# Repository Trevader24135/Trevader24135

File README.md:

Hi! I'm Trevor (@Trevader24135)

I have a bachelor's degree in Electrical Engineering, and have been programming since I was 8 years old! My current obsession is with Rust, but Python has cemented a place in my heart as my first love.

I love Digital Signal Processing, and performing real-time signal analysis for Software-Defined-Radio operations is my area of expertise. I would like to learn more about FPGAs to do the specialized processing more efficiently there, but doing it simply on a CPU (or GPU!) in a compiled language is good enough for most of my day-to-day use cases.

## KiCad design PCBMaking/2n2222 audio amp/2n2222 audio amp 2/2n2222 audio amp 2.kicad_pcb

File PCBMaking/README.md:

# PCBMaking

Recently, I tried making a mini-CNC to mill PCBs. This project ended up failing, mostly due to it not being stiff enough. I likely cheaped out too much on the materials, and probably the spindle too. It worked a bit though, and I tried milling a few PCBs with mixed results. Honestly, mostly negative, but at least I gained some experience with the open-source KiCad software for designing PCBs, which was quite a bit of fun.

<table>
    <tr>
        <td>Project</td>
        <td>Description</td>
    </tr>
    <tr>
        <td>2n2222 audio amp</td>
        <td>This project was meant to be a simple test of my PCB milling capabilities. I actually managed to get a somewhat successful PCB from this one, but it didn't work that well. Probably because I hadn't learned transistor-based circuit analysis and I honestly didn't know what I was doing. It was neat to see it come together though.</td>
    </tr>
    <tr>
        <td>ATmega8U2 breakout</td>
        <td>Had my milling proven more successful and able to mill smaller traces, I was sort of planning on getting some ATmega 8U2 ICs and putting them on breakout boards to use in projects. Oh well, I'll do that when I build an actually-working mill.</td>
    </tr>
    <tr>
        <td>CNC-Trace-Stress-Test</td>
        <td>This was a simple stress test of basic traces of varying thicknesses. I managed to mostly get the 0.4mm trace, but I more reliably managed the 0.5 and larger. Though, this was with a wide clearance, and I couldn't put them as close as I wanted.</td>
    </tr>
    <tr>
        <td>RGB-ShiftRegister</td>
        <td>More of a test of my PCB-making skills, I designed this simple board to try to multiplex some RGB LEDs with a shift register and a microcontroller. This never made it to production as the traces were too close and small for my crappy PCB-mill.</td>
    </tr>
    <tr>
        <td>ShiftRegisterLEDs</td>
        <td>Same concept as the last one, but simplified to have a better chance of working. No transistors and no RGB, just simple LEDs to test it out. It still never made production.</td>
    </tr>
    <tr>
        <td>TylerMoon</td>
        <td>If the PCB milling had worked out, I had planned on making a custom PCB and using a microcontroller to light up a 3D printed moon in lunar phases for my brother. This was never finished in PCB layout because I got discouraged when my mill didn't work out well enough and didn't bother finishing it (and because it wasn't going to lay out that nicely with what I had planned anyways)</td>
    </tr>
</table>

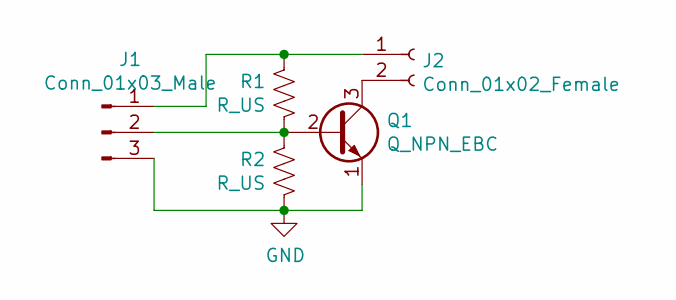
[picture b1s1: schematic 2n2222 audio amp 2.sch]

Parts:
J1: Conn_01x03_Male; PinSocket_1x03_P2.54mm_Vertical
J2: Conn_01x02_Female; PinSocket_1x02_P2.54mm_Vertical
Q1: Q_NPN_EBC; TO-92L_Inline
R1, R2: R_US; R_Axial_DIN0204_L3.6mm_D1.6mm_P7.62mm_Horizontal

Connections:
GND: J1.3, Q1.1 (E), R2.1
unnamed: J1.1, J2.1, R1.2
unnamed: J1.2, Q1.2 (B), R1.1, R2.2
unnamed: J2.2, Q1.3 (C)

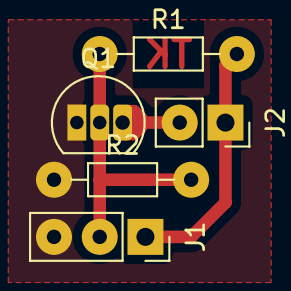
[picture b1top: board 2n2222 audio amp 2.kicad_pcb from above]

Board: 2 copper layers, 5 parts (0 on the bottom side), 4 nets.

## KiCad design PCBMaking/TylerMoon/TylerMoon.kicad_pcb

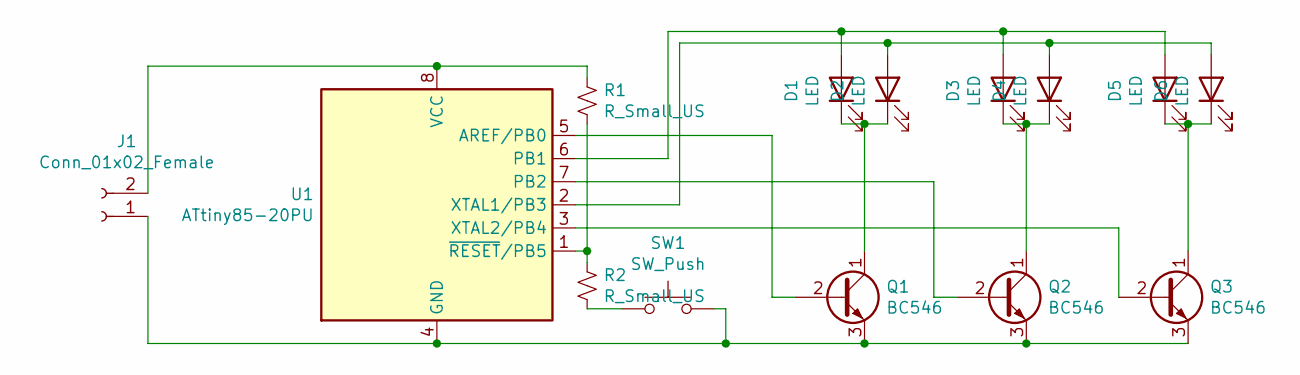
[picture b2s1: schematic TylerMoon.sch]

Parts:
D1, D2, D3, D4, D5, D6: LED; LED_D3.0mm
J1: Conn_01x02_Female; PinSocket_1x02_P2.54mm_Vertical
Q1, Q2, Q3: BC546; TO-92_Inline
R1, R2: R_Small_US; R_Axial_DIN0204_L3.6mm_D1.6mm_P7.62mm_Horizontal
SW1: SW_Push; SW_Tactile_Straight_KSA0Axx1LFTR
U1: ATtiny85-20PU; DIP-8_W7.62mm

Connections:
unnamed: D1.1 (K), D2.1 (K), Q1.1 (C)
unnamed: D1.2 (A), D3.2 (A), D5.2 (A), U1.6 (PB1)
unnamed: D2.2 (A), D4.2 (A), D6.2 (A), U1.2 (XTAL1/PB3)
unnamed: D3.1 (K), D4.1 (K), Q2.1 (C)
unnamed: D5.1 (K), D6.1 (K), Q3.1 (C)
unnamed: J1.1, Q1.3 (E), Q2.3 (E), Q3.3 (E), SW1.2, U1.4 (GND)
unnamed: J1.2, R1.1, U1.8 (VCC)
unnamed: Q1.2 (B), U1.5 (AREF/PB0)
unnamed: Q2.2 (B), U1.7 (PB2)
unnamed: Q3.2 (B), U1.3 (XTAL2/PB4)
unnamed: R1.2, R2.1, U1.1 (~RESET~/PB5)
unnamed: R2.2, SW1.1

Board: 2 copper layers, 14 parts (0 on the bottom side), 12 nets, no tracks yet.

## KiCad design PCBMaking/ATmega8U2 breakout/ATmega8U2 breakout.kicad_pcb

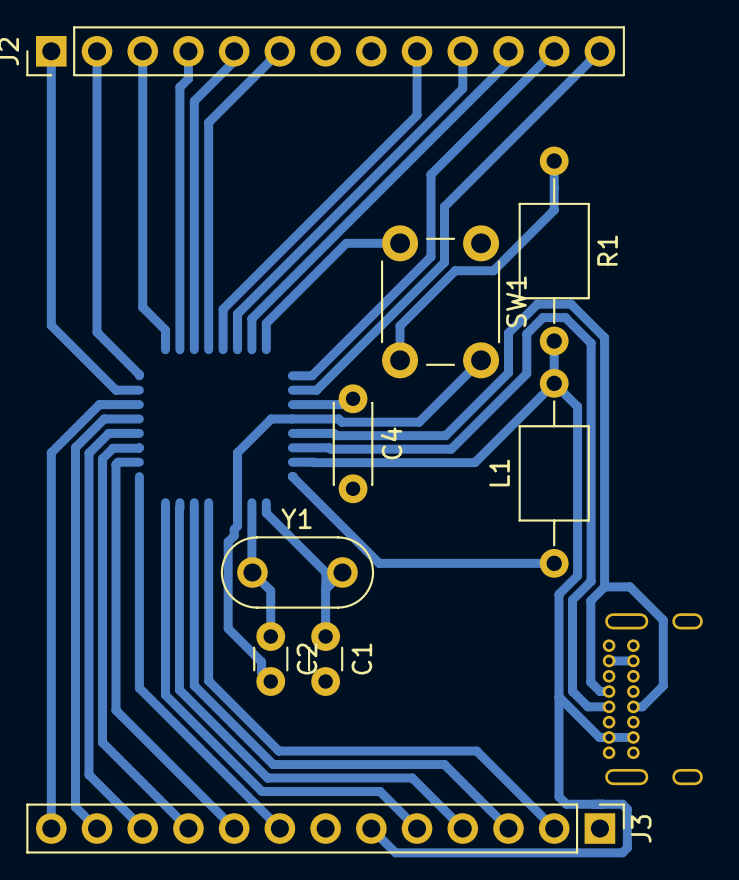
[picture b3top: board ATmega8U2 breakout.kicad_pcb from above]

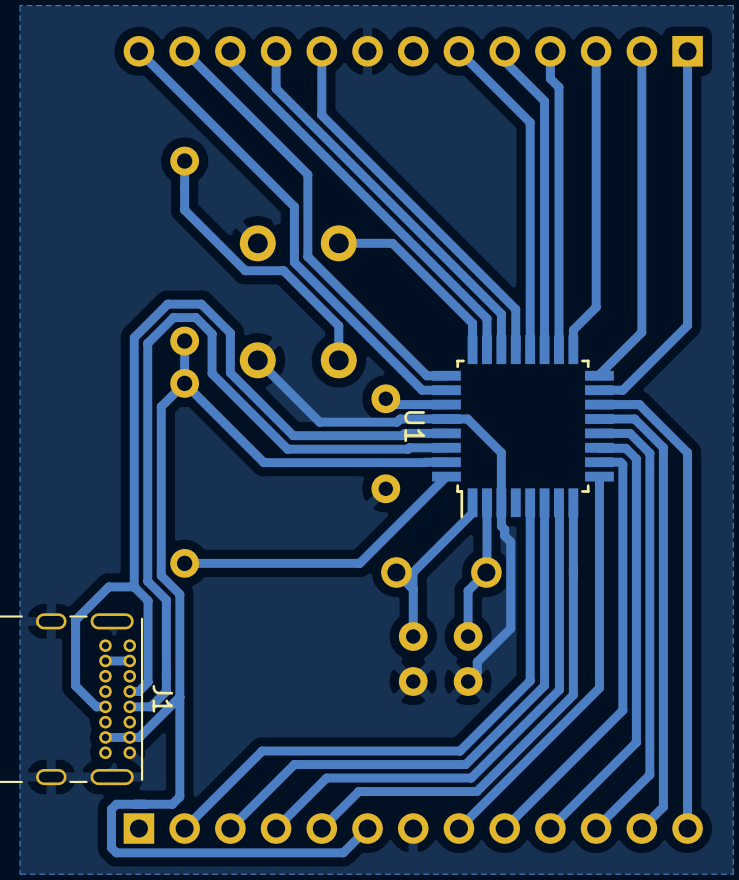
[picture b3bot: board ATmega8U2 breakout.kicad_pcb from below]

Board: 2 copper layers, 11 parts (2 on the bottom side), 30 nets.

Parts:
C1, C2: C; C_Disc_D3.0mm_W1.6mm_P2.50mm
C4: C; C_Disc_D4.3mm_W1.9mm_P5.00mm
J1: USB_C_Receptacle_USB2.0; USB_C_Receptacle_GCT_USB4085
J2, J3: Conn_01x13_Male; PinHeader_1x13_P2.54mm_Vertical
L1: L; L_Axial_L5.0mm_D3.6mm_P10.00mm_Horizontal_Murata_BL01RN1A2A2
R1: R_Small_US; L_Axial_L5.0mm_D3.6mm_P10.00mm_Horizontal_Murata_BL01RN1A2A2
SW1: SW_Push_Open_Dual; SW_PUSH_6mm
U1: ATmega8U2-AU; TQFP-32_7x7mm_P0.8mm
Y1: Crystal; Resonator-2Pin_W8.0mm_H3.5mm

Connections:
GND: C1.2, C2.2, C4.2, J1.A1, J1.A12, J1.B1, J1.B12, J1.S1, J2.8, J3.7, SW1.1, U1.3, U1.28
unnamed: C1.1, U1.1, Y1.2
unnamed: C2.1, U1.2, Y1.1
unnamed: C4.1, U1.27
unnamed: J1.A4, J1.A9, J1.B4, J1.B9, J2.7, J3.6, L1.2, R1.2, U1.31
unnamed: J1.A6, J1.B6, U1.29
unnamed: J1.A7, J1.B7, U1.30
unnamed: J2.1, U1.15
unnamed: J2.2, U1.16
unnamed: J2.3, U1.17
unnamed: J2.4, U1.18
unnamed: J2.5, U1.19
unnamed: J2.6, U1.20
unnamed: J2.9, U1.21
unnamed: J2.10, U1.22
unnamed: J2.11, U1.23
unnamed: J2.12, U1.25
unnamed: J2.13, U1.26
unnamed: J3.1, R1.1, SW1.2, U1.24
unnamed: J3.2, U1.5
unnamed: J3.3, U1.6
unnamed: J3.4, U1.7
unnamed: J3.5, U1.8
unnamed: J3.8, U1.9
unnamed: J3.9, U1.10
unnamed: J3.10, U1.11
unnamed: J3.11, U1.12
unnamed: J3.12, U1.13
unnamed: J3.13, U1.14
unnamed: L1.1, U1.32

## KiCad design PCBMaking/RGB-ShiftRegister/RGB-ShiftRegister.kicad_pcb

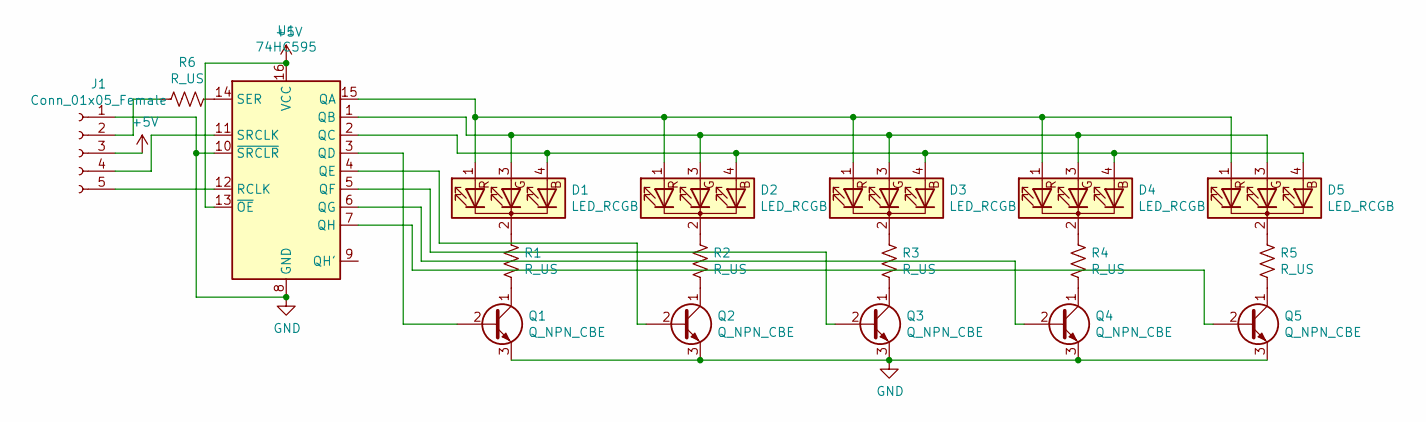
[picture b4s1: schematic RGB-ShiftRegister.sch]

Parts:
D1, D2, D3, D4, D5: LED_RCGB; LED_D5.0mm-4_RGB
J1: Conn_01x05_Female; PinSocket_1x05_P2.54mm_Vertical
Q1, Q2, Q3, Q4, Q5: Q_NPN_CBE; TO-92L_Inline
R1, R2, R3, R4, R5: R_US; R_Axial_DIN0204_L3.6mm_D1.6mm_P7.62mm_Horizontal
R6: R_US; R_Axial_DIN0309_L9.0mm_D3.2mm_P12.70mm_Horizontal
U1: 74HC595; DIP-16_W7.62mm_LongPads

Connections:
+5V: J1.3, U1.13 (~OE), U1.16 (VCC)
GND: J1.1, Q1.3 (E), Q2.3 (E), Q3.3 (E), Q4.3 (E), Q5.3 (E), U1.8 (GND), U1.10 (~SRCLR)
unnamed: D1.1 (RA), D2.1 (RA), D3.1 (RA), D4.1 (RA), D5.1 (RA), U1.15 (QA)
unnamed: D1.2 (K), R1.1
unnamed: D1.3 (GA), D2.3 (GA), D3.3 (GA), D4.3 (GA), D5.3 (GA), U1.1 (QB)
unnamed: D1.4 (BA), D2.4 (BA), D3.4 (BA), D4.4 (BA), D5.4 (BA), U1.2 (QC)
unnamed: D2.2 (K), R2.1
unnamed: D3.2 (K), R3.1
unnamed: D4.2 (K), R4.1
unnamed: D5.2 (K), R5.1
unnamed: J1.2, R6.2
unnamed: J1.4, U1.11 (SRCLK)
unnamed: J1.5, U1.12 (RCLK)
unnamed: Q1.1 (C), R1.2
unnamed: Q1.2 (B), U1.3 (QD)
unnamed: Q2.1 (C), R2.2
unnamed: Q2.2 (B), U1.4 (QE)
unnamed: Q3.1 (C), R3.2
unnamed: Q3.2 (B), U1.5 (QF)
unnamed: Q4.1 (C), R4.2
unnamed: Q4.2 (B), U1.6 (QG)
unnamed: Q5.1 (C), R5.2
unnamed: Q5.2 (B), U1.7 (QH)
unnamed: R6.1, U1.14 (SER)

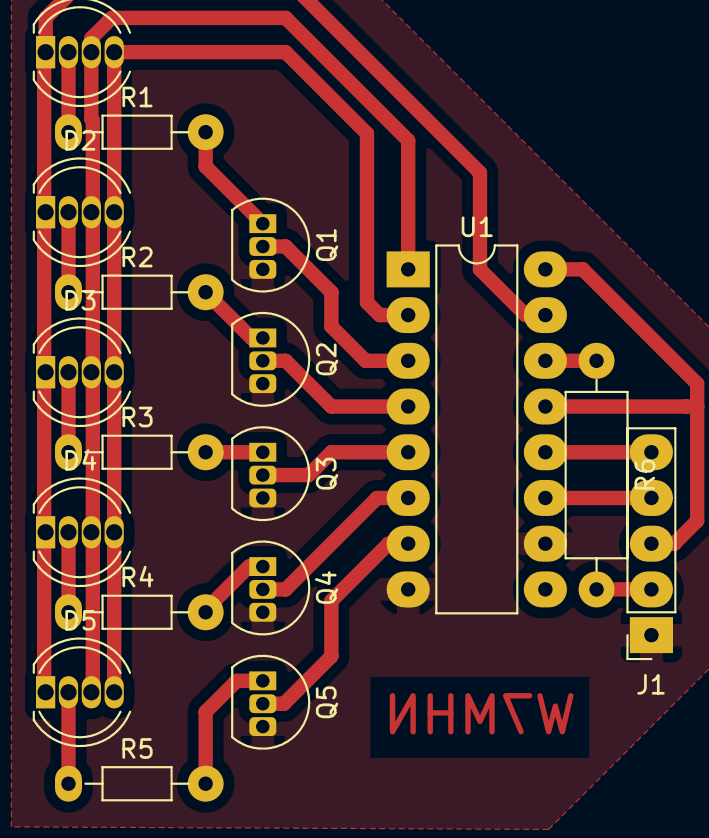
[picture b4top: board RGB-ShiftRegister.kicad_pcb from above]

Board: 2 copper layers, 18 parts (0 on the bottom side), 24 nets.

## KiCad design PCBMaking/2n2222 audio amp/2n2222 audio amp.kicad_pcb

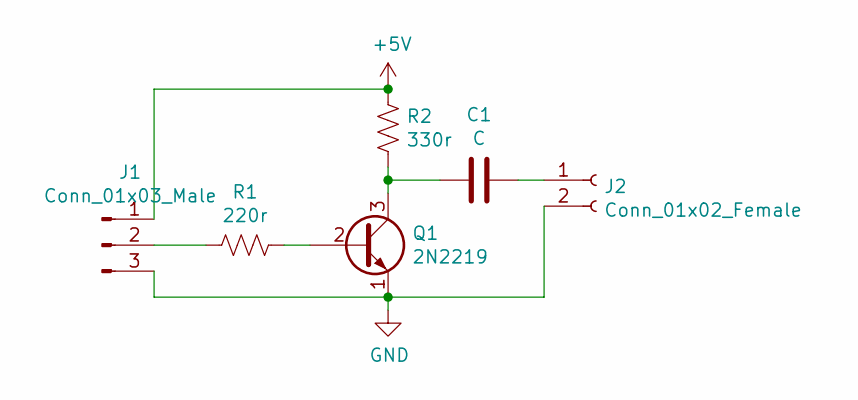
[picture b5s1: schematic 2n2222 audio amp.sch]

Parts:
C1: C; C_Rect_L9.0mm_W2.5mm_P7.50mm_MKT
J1: Conn_01x03_Male; JST_EH_B3B-EH-A_1x03_P2.50mm_Vertical
J2: Conn_01x02_Female; PinSocket_1x02_P2.54mm_Vertical
Q1: 2N2219; TO-92L_Wide
R1: 220r; R_Axial_DIN0204_L3.6mm_D1.6mm_P2.54mm_Vertical
R2: 330r; R_Axial_DIN0204_L3.6mm_D1.6mm_P2.54mm_Vertical

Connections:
+5V: J1.1, R2.1
GND: J1.3, J2.2, Q1.1 (E)
unnamed: C1.1, J2.1
unnamed: C1.2, Q1.3 (C), R2.2
unnamed: J1.2, R1.2
unnamed: Q1.2 (B), R1.1

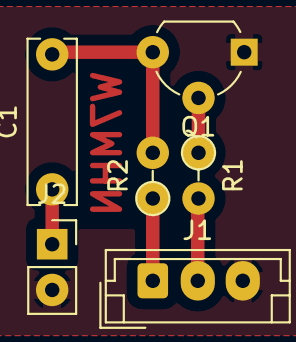
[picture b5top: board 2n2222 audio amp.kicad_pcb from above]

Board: 2 copper layers, 6 parts (0 on the bottom side), 6 nets.

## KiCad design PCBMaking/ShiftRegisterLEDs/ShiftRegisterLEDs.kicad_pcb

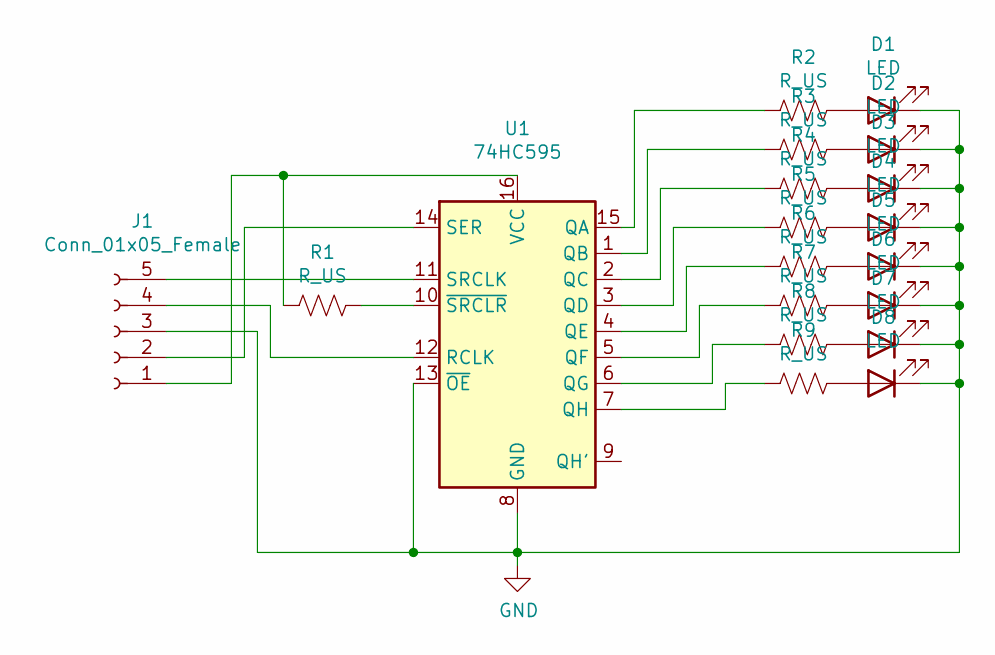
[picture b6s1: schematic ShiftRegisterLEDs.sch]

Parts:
D1, D2, D3, D4, D5, D6, D7, D8: LED; LED_D3.0mm
J1: Conn_01x05_Female; JST_XH_B5B-XH-A_1x05_P2.50mm_Vertical
R1, R2, R3, R4, R5, R6, R7, R8, R9: R_US; R_Axial_DIN0207_L6.3mm_D2.5mm_P7.62mm_Horizontal
U1: 74HC595; DIP-16_W7.62mm

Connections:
GND: D1.1 (K), D2.1 (K), D3.1 (K), D4.1 (K), D5.1 (K), D6.1 (K), D7.1 (K), D8.1 (K), J1.3, U1.8 (GND), U1.13 (~OE)
unnamed: D1.2 (A), R2.1
unnamed: D2.2 (A), R3.1
unnamed: D3.2 (A), R4.1
unnamed: D4.2 (A), R5.1
unnamed: D5.2 (A), R6.1
unnamed: D6.2 (A), R7.1
unnamed: D7.2 (A), R8.1
unnamed: D8.2 (A), R9.1
unnamed: J1.1, R1.2, U1.16 (VCC)
unnamed: J1.2, U1.14 (SER)
unnamed: J1.4, U1.12 (RCLK)
unnamed: J1.5, U1.11 (SRCLK)
unnamed: R1.1, U1.10 (~SRCLR)
unnamed: R2.2, U1.15 (QA)
unnamed: R3.2, U1.1 (QB)
unnamed: R4.2, U1.2 (QC)
unnamed: R5.2, U1.3 (QD)
unnamed: R6.2, U1.4 (QE)
unnamed: R7.2, U1.5 (QF)
unnamed: R8.2, U1.6 (QG)
unnamed: R9.2, U1.7 (QH)

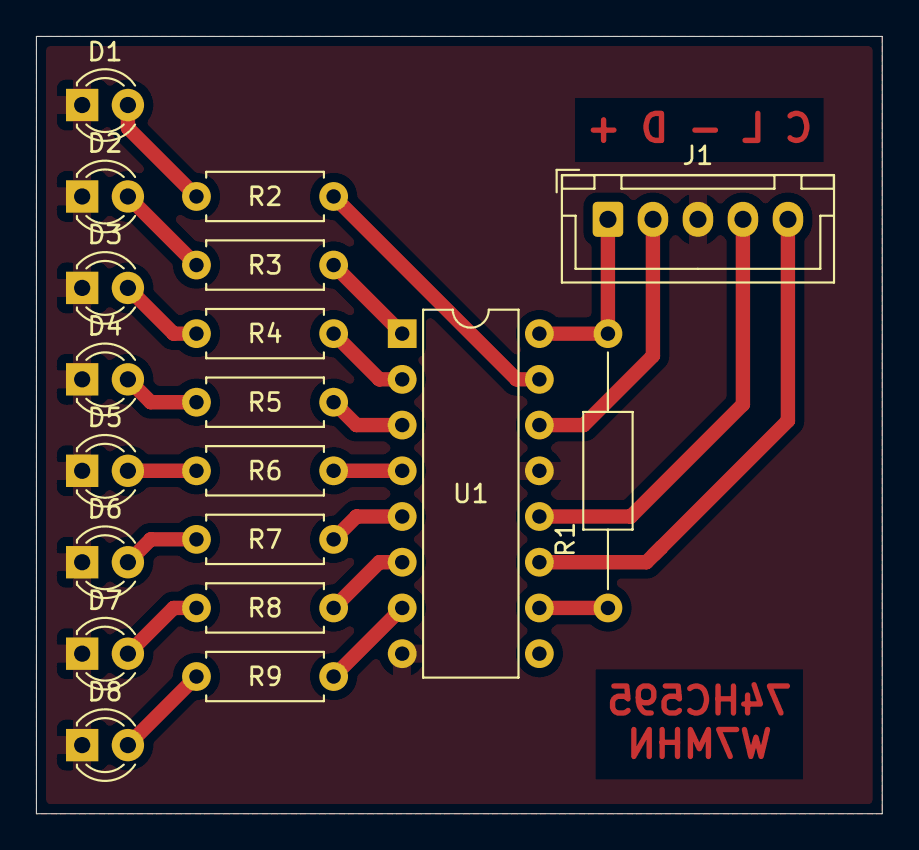
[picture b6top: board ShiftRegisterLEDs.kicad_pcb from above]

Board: 2 copper layers, 47.0 x 43.2 mm, 19 parts (0 on the bottom side), 22 nets.

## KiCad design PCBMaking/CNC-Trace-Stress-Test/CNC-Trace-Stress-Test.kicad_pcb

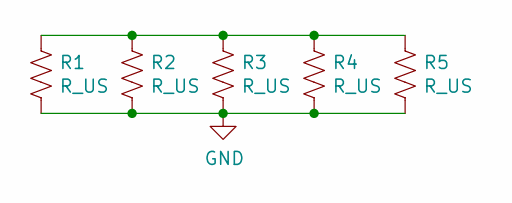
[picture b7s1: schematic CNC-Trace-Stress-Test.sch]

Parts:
R1, R2, R3, R4, R5: R_US; R_Axial_DIN0204_L3.6mm_D1.6mm_P7.62mm_Horizontal

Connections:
GND: R1.2, R2.2, R3.2, R4.2, R5.2
unnamed: R1.1, R2.1, R3.1, R4.1, R5.1

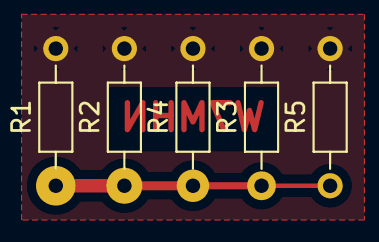
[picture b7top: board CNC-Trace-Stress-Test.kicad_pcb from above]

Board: 2 copper layers, 5 parts (0 on the bottom side), 2 nets.

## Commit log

2021-05-03 Initial Push
2021-05-04 ECEN160 and CSE210
    the final projects for ECEN 160 and CSE 210 have been added to the portfolio.
2021-05-04 actually pushed CSE210
    the git config in CSE210 prevented pushing
2021-05-04 Main Readme gets link
2021-05-04 AutoHotKey scripts
    A push of most of my daily-driver AutoHotKey scripts.
2021-05-04 PrintDragon project added
2021-05-04 PrintDragon Typo Fix
2021-05-04 Pretimer asembly screwery
2021-05-04 -Protogame build files
2021-05-04 AssemblyFibonacci
2021-05-05 assembler LCD beginnings
2021-05-05 More Projects 5/5/21
    Past projects, C helper code, and PCB layout projects.
2021-05-05 DragonCNC
2021-06-01 Rust & Rust Euler001-Euler008
2021-06-01 Euler001 - Euler008 upload
2021-06-01 Euler001 - Euler007
    I needed to remove the cargo-generated gitignore files and git directory from the rust projects.
2021-06-01 gitattributes to remove makefile from summary 0.1
